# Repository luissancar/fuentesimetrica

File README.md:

# Fuente de alimentación simétrica
## Esquema y pcb formato Eagle de una fuente de +15 0 -15
## Cambiando los 78XX, 79XX se puede utizar para otras tensiones.

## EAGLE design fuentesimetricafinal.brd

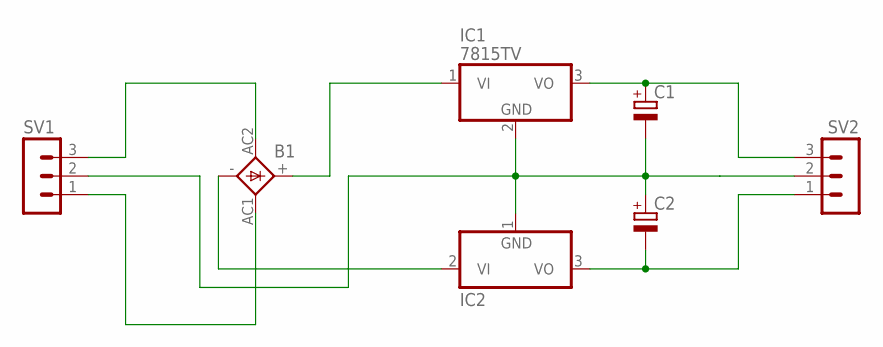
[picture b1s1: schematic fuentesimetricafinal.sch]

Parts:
B1: FBU4
C1, C2: CPOL-EUE3.5-8; E3,5-8
IC1: 7815TV; TO220V
IC2: 7915T; TO220H
SV1, SV2: MA03-1

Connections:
GND: C1.-, C2.+, IC1.2 (GND), IC2.1 (GND), SV1.2, SV2.2
unnamed: B1.AC2 (AC1), SV1.3
unnamed: B1.AC1 (AC2), SV1.1
unnamed: B1.-, IC2.2 (VI)
unnamed: B1.+, IC1.1 (VI)
unnamed: C1.+, IC1.3 (VO), SV2.3
unnamed: C2.-, IC2.3 (VO), SV2.1

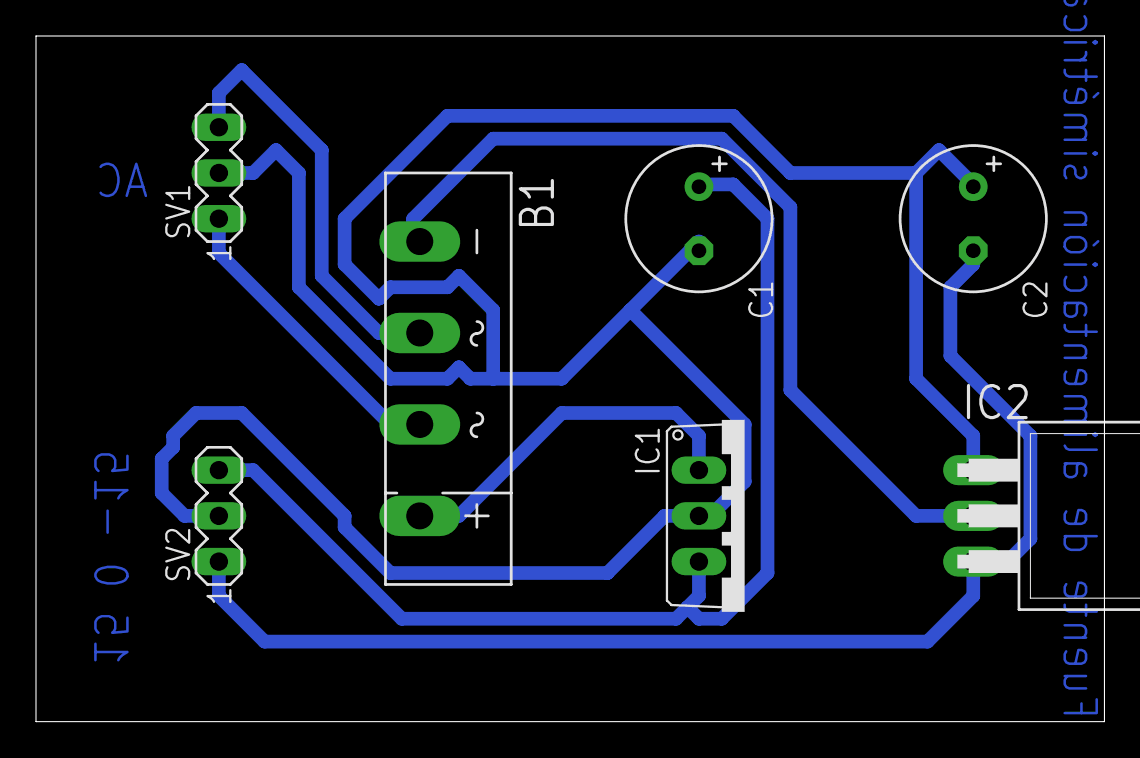
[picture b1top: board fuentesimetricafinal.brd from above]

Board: 2 copper layers, 59.4 x 38.1 mm, 7 parts (0 on the bottom side), 7 nets.

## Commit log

2016-12-09 fuente
2016-12-09 Commit messagef
2016-12-12 modificada la pcb
